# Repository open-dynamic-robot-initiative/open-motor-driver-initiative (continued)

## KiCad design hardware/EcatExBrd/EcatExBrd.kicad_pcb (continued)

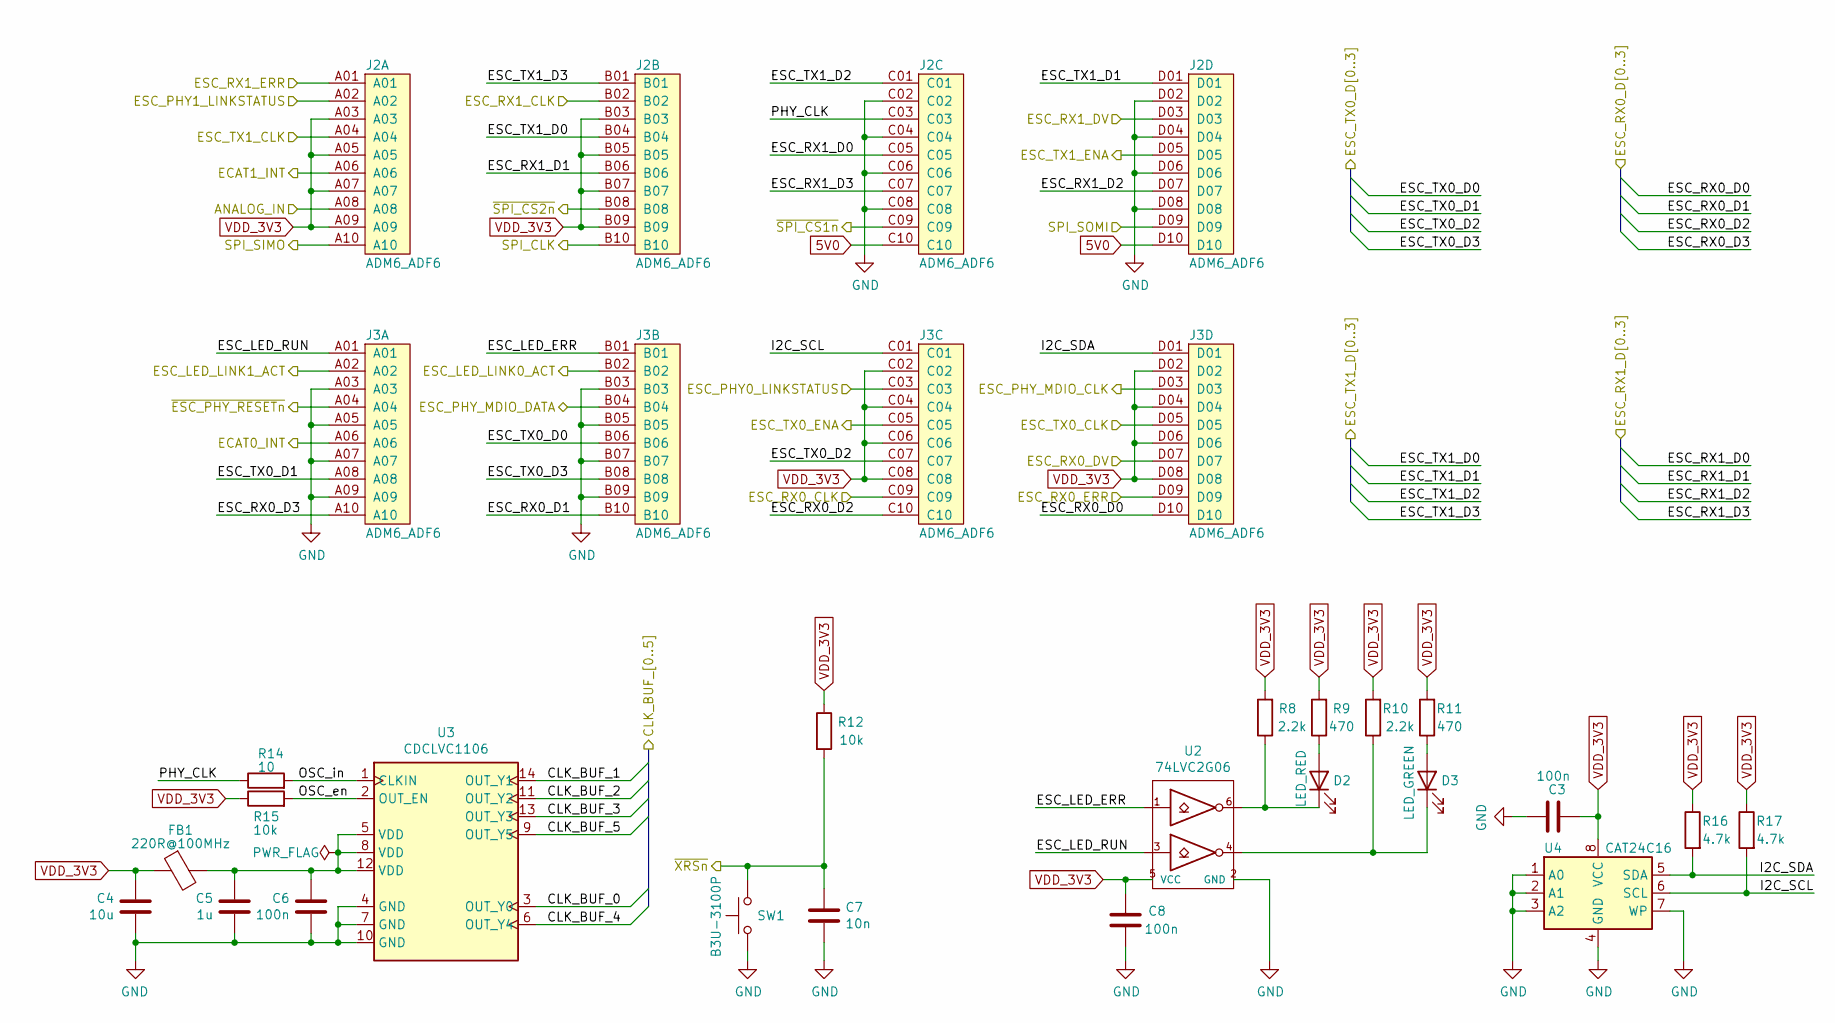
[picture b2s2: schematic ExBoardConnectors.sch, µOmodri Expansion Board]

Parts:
C3, C6, C8: 100n; C_0201_0603Metric; Part No GRM033R61C104KE84D; DigiKey 490-9985-1-ND
C4: 10u; C_0402_1005Metric; Part No GRM155R60J106ME15D; DigiKey 490-13238-1-ND
C5: 1u; C_0201_0603Metric; Part No GRM033R61A105ME15D; DigiKey 490-13226-1-ND
C7: 10n; C_0201_0603Metric; Part No GRM033R71E103KE14D; DigiKey 490-14454-1-ND
D2: LED_RED; LED_0402_1005Metric; Part No HSMC-C280; DigiKey 516-3060-1-ND
D3: LED_GREEN; LED_0402_1005Metric; Part No HSMG-C280; DigiKey 516-3066-1-ND
FB1: 220R@100MHz; L_0603_1608Metric; Part No BLM18SG221TN1D; DigiKey 490-5225-1-ND
J2, J3: ADM6_ADF6; ADM6-10-XX.X-XXX-4-X-A-XR; Part No ADM6-10-01.5-L-4-2-A-TR; DigiKey 612-ADM6-10-01.5-L-4-2-A-TR-ND
R8, R10: 2.2k; R_0201_0603Metric; Part No ERJ-1GNF2201C; DigiKey P122832CT-ND
R9, R11: 470; R_0201_0603Metric; Part No ERJ-1GNF4700C; DigiKey P123030CT-ND
R12, R15: 10k; R_0201_0603Metric; Part No ERJ-1GNF1002C; DigiKey P122414CT-ND
R14: 10; R_0201_0603Metric; Part No ERJ-1GNF10R0C; DigiKey P122669CT-ND
R16, R17: 4.7k; R_0201_0603Metric; Part No ERJ-1GNF4701C; DigiKey P123031CT-ND
SW1: B3U-3100P; SW_SPST_B3U-1000P; Part No B3U-1000P; DigiKey SW1020CT-ND
U2: 74LVC2G06; USON-6_P0.5mm_1x1.5mm; Part No SN74LVC2G06DRY; DigiKey 296-34873-1-ND
U3: CDCLVC1106; TSSOP-14_4.4x5mm_P0.65mm; Part No CDCLVC1106PWR; DigiKey 296-27588-1-ND
U4: CAT24C16; DFN-8-1EP_3x2mm_P0.5mm_EP1.3x1.5mm; Part No CAT24C16HU4I-GT3; DigiKey CAT24C16HU4I-GT3OSCT-ND

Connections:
5V0: J2.C10, J2.D10; also elsewhere on the board
/ECAT_0 - PHY/25MHz_OSC_in: U3.6 (OUT_Y4); also elsewhere on the board
/ECAT_0 - PHY/ECAT_RX_CLK: J3.C09; also elsewhere on the board
/ECAT_0 - PHY/ECAT_RX_D0: J3.D10; also elsewhere on the board
/ECAT_0 - PHY/ECAT_RX_D1: J3.B10; also elsewhere on the board
/ECAT_0 - PHY/ECAT_RX_D2: J3.C10; also elsewhere on the board
/ECAT_0 - PHY/ECAT_RX_D3: J3.A10; also elsewhere on the board
/ECAT_0 - PHY/ECAT_RX_DV: J3.D07; also elsewhere on the board
/ECAT_0 - PHY/ECAT_RX_ER: J3.D09; also elsewhere on the board
/ECAT_0 - PHY/ECAT_TX_CLK: J3.D05; also elsewhere on the board
/ECAT_0 - PHY/ECAT_TX_D0: J3.B06; also elsewhere on the board
/ECAT_0 - PHY/ECAT_TX_D1: J3.A08; also elsewhere on the board
/ECAT_0 - PHY/ECAT_TX_D2: J3.C07; also elsewhere on the board
/ECAT_0 - PHY/ECAT_TX_D3: J3.B08; also elsewhere on the board
/ECAT_0 - PHY/ECAT_TX_EN: J3.C05; also elsewhere on the board
/ECAT_1 - PHY/25MHz_OSC_in: U3.3 (OUT_Y0); also elsewhere on the board
/ECAT_1 - PHY/ECAT_RX_CLK: J2.B02; also elsewhere on the board
/ECAT_1 - PHY/ECAT_RX_D0: J2.C05; also elsewhere on the board
/ECAT_1 - PHY/ECAT_RX_D1: J2.B06; also elsewhere on the board
/ECAT_1 - PHY/ECAT_RX_D2: J2.D07; also elsewhere on the board
/ECAT_1 - PHY/ECAT_RX_D3: J2.C07; also elsewhere on the board
/ECAT_1 - PHY/ECAT_RX_DV: J2.D03; also elsewhere on the board
/ECAT_1 - PHY/ECAT_RX_ER: J2.A01; also elsewhere on the board
/ECAT_1 - PHY/ECAT_TX_CLK: J2.A04; also elsewhere on the board
/ECAT_1 - PHY/ECAT_TX_D0: J2.B04; also elsewhere on the board
/ECAT_1 - PHY/ECAT_TX_D1: J2.D01; also elsewhere on the board
/ECAT_1 - PHY/ECAT_TX_D2: J2.C01; also elsewhere on the board
/ECAT_1 - PHY/ECAT_TX_D3: J2.B01; also elsewhere on the board
/ECAT_1 - PHY/ECAT_TX_EN: J2.D05; also elsewhere on the board
/ECAT_Extension/ANALOG_IN: J2.A08; also elsewhere on the board
/ECAT_Extension/ECAT0_INT: J3.A06; also elsewhere on the board
/ECAT_Extension/ECAT1_INT: J2.A06; also elsewhere on the board
/ECAT_Extension/ESC_LED_ERR: J3.B01, U2.1
/ECAT_Extension/ESC_LED_LINK0_ACT: J3.B02; also elsewhere on the board
/ECAT_Extension/ESC_LED_LINK1_ACT: J3.A02; also elsewhere on the board
/ECAT_Extension/ESC_LED_RUN: J3.A01, U2.3
/ECAT_Extension/ESC_PHY0_LINKSTATUS: J3.C03; also elsewhere on the board
/ECAT_Extension/ESC_PHY1_LINKSTATUS: J2.A02; also elsewhere on the board
/ECAT_Extension/ESC_PHY_MDIO_CLK: J3.D03; also elsewhere on the board
/ECAT_Extension/ESC_PHY_MDIO_DATA: J3.B04; also elsewhere on the board
/ECAT_Extension/I2C_SCL: J3.C01, R17.2, U4.6 (SCL)
/ECAT_Extension/I2C_SDA: J3.D01, R16.2, U4.5 (SDA)
/ECAT_Extension/OSC_en: R15.2, U3.2 (OUT_EN)
/ECAT_Extension/OSC_in: R14.2, U3.1 (CLKIN)
/ECAT_Extension/PHY_CLK: J2.C03, R14.1
/ECAT_Extension/~ESC_PHY_RESETn~: J3.A04; also elsewhere on the board
/ECAT_Extension/~SPI_CS1n~: J2.C09; also elsewhere on the board
/ECAT_Extension/~SPI_CS2n~: J2.B08; also elsewhere on the board
/Sensor Channel #1/25MHz_OSC_in_1: U3.13 (OUT_Y3); also elsewhere on the board
/Sensor Channel #1/25MHz_OSC_in_2: U3.14 (OUT_Y1); also elsewhere on the board
/Sensor Channel #1/MISO: J2.D09; also elsewhere on the board
/Sensor Channel #1/MOSI: J2.A10; also elsewhere on the board
/Sensor Channel #1/SCLK: J2.B10; also elsewhere on the board
/Sensor Channel #1/~RST_n~: C7.1, R12.2, SW1.2; also elsewhere on the board
/Sensor Channel #2/25MHz_OSC_in_1: U3.9 (OUT_Y5); also elsewhere on the board
/Sensor Channel #2/25MHz_OSC_in_2: U3.11 (OUT_Y2); also elsewhere on the board
GND: C3.1, C4.2, C5.2, C6.2, C7.2, C8.2, J2.C02, J2.C04, J2.C06, J2.C08, J2.D02, J2.D04, J2.D06, J2.D08, J3.A03, J3.A05, J3.A07, J3.A09, J3.B03, J3.B05, J3.B07, J3.B09, SW1.1, U2.2 (GND), U3.4 (GND), U3.7 (GND), U3.10 (GND), U4.1 (A0), U4.2 (A1), U4.3 (A2), U4.4 (GND), U4.7 (WP), U4.9 (GND); also elsewhere on the board
unnamed: C5.1, C6.1, FB1.2, U3.5 (VDD), U3.8 (VDD), U3.12 (VDD)
unnamed: D2.1 (K), R8.1, U2.6
unnamed: D2.2 (A), R9.1
unnamed: D3.1 (K), R10.1, U2.4
unnamed: D3.2 (A), R11.1
VDD_3V3: C3.2, C4.1, C8.1, FB1.1, J2.A03, J2.A05, J2.A07, J2.A09, J2.B03, J2.B05, J2.B07, J2.B09, J3.C02, J3.C04, J3.C06, J3.C08, J3.D02, J3.D04, J3.D06, J3.D08, R8.2, R9.2, R10.2, R11.2, R12.1, R15.1, R16.1, R17.1, U2.5 (VCC), U4.8 (VCC); also elsewhere on the board

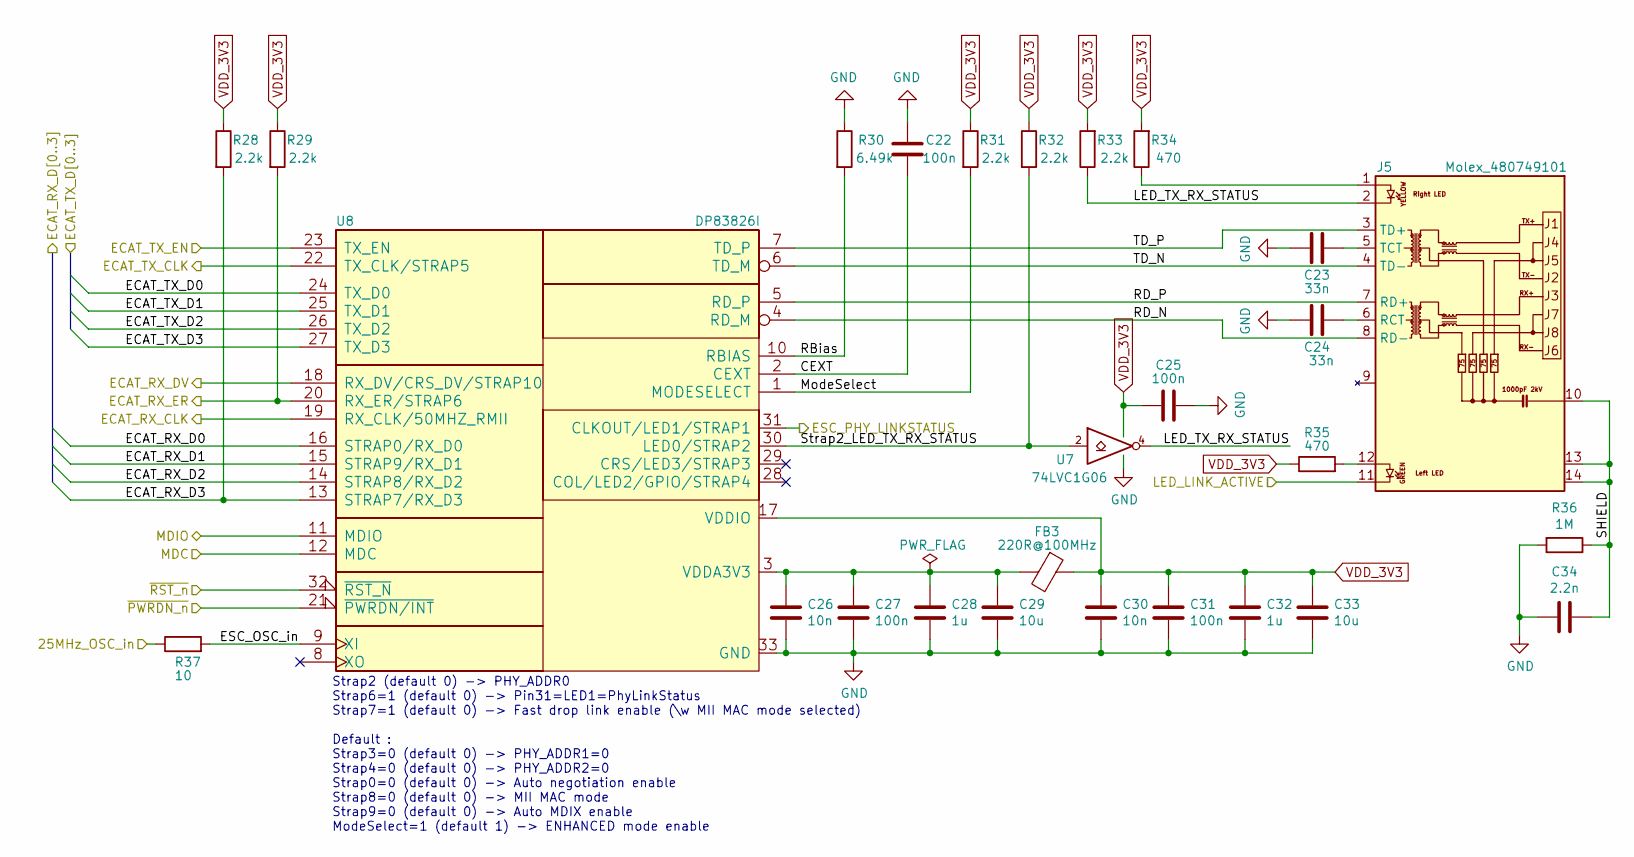
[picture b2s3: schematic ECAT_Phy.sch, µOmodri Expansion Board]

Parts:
C9, C12, C14, C18: 100n; C_0201_0603Metric; Part No GRM033R61C104KE84D; DigiKey 490-9985-1-ND
C10, C11: 33n; C_0201_0603Metric; Part No GRM033R61C333KE84D; DigiKey 490-7226-1-ND
C13, C17: 10n; C_0201_0603Metric; Part No GRM033R71E103KE14D; DigiKey 490-14454-1-ND
C15, C19: 1u; C_0201_0603Metric; Part No GRM033R61A105ME15D; DigiKey 490-13226-1-ND
C16, C20: 10u; C_0402_1005Metric; Part No GRM155R60J106ME15D; DigiKey 490-13238-1-ND
C21: 2.2n; C_0603_1608Metric; Part No GRM188R72D222KW07D; DigiKey 490-16804-1-ND
FB2: 220R@100MHz; L_0603_1608Metric; Part No BLM18SG221TN1D; DigiKey 490-5225-1-ND
J4: Molex_480749101; RJ45_Molex_48074-9101_Horizontal; Part No 48074-9101; DigiKey WM17279CT-ND
R18, R19, R21, R22, R23: 2.2k; R_0201_0603Metric; Part No ERJ-1GNF2201C; DigiKey P122832CT-ND
R20: 6.49k; R_0201_0603Metric; Part No ERJ-1GNF6491C; DigiKey P123115CT-ND
R24, R25: 470; R_0201_0603Metric; Part No ERJ-1GNF4700C; DigiKey P123030CT-ND
R26: 1M; R_0805_2012Metric; Part No ERJ-6ENF1004V; DigiKey P1.00MCCT-ND
R27: 10; R_0201_0603Metric; Part No ERJ-1GNF10R0C; DigiKey P122669CT-ND
U5: 74LVC1G06; USON-6_P0.5mm_1x1.5mm; Part No SN74LVC1G06DRY; DigiKey 296-29047-1-ND
U6: DP83826I; VQFN-32-1EP_5x5mm_P0.5mm_EP2.2x2.2mm; Part No DP83826IRHBR; DigiKey 296-DP83826IRHBRCT-ND

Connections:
/ECAT_0 - PHY/25MHz_OSC_in: R27.1; also elsewhere on the board
/ECAT_0 - PHY/CEXT: C9.1, U6.2 (CEXT)
/ECAT_0 - PHY/ECAT_RX_CLK: U6.19 (RX_CLK/50MHZ_RMII); also elsewhere on the board
/ECAT_0 - PHY/ECAT_RX_D0: U6.16 (STRAP0/RX_D0); also elsewhere on the board
/ECAT_0 - PHY/ECAT_RX_D1: U6.15 (STRAP9/RX_D1); also elsewhere on the board
/ECAT_0 - PHY/ECAT_RX_D2: U6.14 (STRAP8/RX_D2); also elsewhere on the board
/ECAT_0 - PHY/ECAT_RX_D3: R18.2, U6.13 (STRAP7/RX_D3); also elsewhere on the board
/ECAT_0 - PHY/ECAT_RX_DV: U6.18 (RX_DV/CRS_DV/STRAP10); also elsewhere on the board
/ECAT_0 - PHY/ECAT_RX_ER: R19.2, U6.20 (RX_ER/STRAP6); also elsewhere on the board
/ECAT_0 - PHY/ECAT_TX_CLK: U6.22 (TX_CLK/STRAP5); also elsewhere on the board
/ECAT_0 - PHY/ECAT_TX_D0: U6.24 (TX_D0); also elsewhere on the board
/ECAT_0 - PHY/ECAT_TX_D1: U6.25 (TX_D1); also elsewhere on the board
/ECAT_0 - PHY/ECAT_TX_D2: U6.26 (TX_D2); also elsewhere on the board
/ECAT_0 - PHY/ECAT_TX_D3: U6.27 (TX_D3); also elsewhere on the board
/ECAT_0 - PHY/ECAT_TX_EN: U6.23 (TX_EN); also elsewhere on the board
/ECAT_0 - PHY/ESC_OSC_in: R27.2, U6.9 (XI)
/ECAT_0 - PHY/LED_TX_RX_STATUS: J4.2, R23.1, U5.4
/ECAT_0 - PHY/ModeSelect: R21.2, U6.1 (MODESELECT)
/ECAT_0 - PHY/RBias: R20.2, U6.10 (RBIAS)
/ECAT_0 - PHY/RD_N: J4.8 (RD-), U6.4 (RD_M)
/ECAT_0 - PHY/RD_P: J4.7 (RD+), U6.5 (RD_P)
/ECAT_0 - PHY/SHIELD: C21.1, J4.10, J4.13, J4.14, R26.1
/ECAT_0 - PHY/Strap2_LED_TX_RX_STATUS: R22.2, U5.2, U6.30 (LED0/STRAP2)
/ECAT_0 - PHY/TD_N: J4.4 (TD-), U6.6 (TD_M)
/ECAT_0 - PHY/TD_P: J4.3 (TD+), U6.7 (TD_P)
/ECAT_Extension/ECAT0_INT: U6.21 (~PWRDN/INT~); also elsewhere on the board
/ECAT_Extension/ESC_LED_LINK0_ACT: J4.11; also elsewhere on the board
/ECAT_Extension/ESC_PHY0_LINKSTATUS: U6.31 (CLKOUT/LED1/STRAP1); also elsewhere on the board
/ECAT_Extension/ESC_PHY_MDIO_CLK: U6.12 (MDC); also elsewhere on the board
/ECAT_Extension/ESC_PHY_MDIO_DATA: U6.11 (MDIO); also elsewhere on the board
/ECAT_Extension/~ESC_PHY_RESETn~: U6.32 (~RST_N~); also elsewhere on the board
GND: C9.2, C10.2, C11.2, C12.1, C13.2, C14.2, C15.2, C16.2, C17.2, C18.2, C19.2, C20.2, C21.2, R20.1, R26.2, U5.3 (GND), U6.33 (GND); also elsewhere on the board
unnamed: C10.1, J4.5 (TCT)
unnamed: C11.1, J4.6 (RCT)
unnamed: C13.1, C14.1, C15.1, C16.1, FB2.2, U6.3 (VDDA3V3)
unnamed: J4.1, R24.1
unnamed: J4.12, R25.2
VDD_3V3: C12.2, C17.1, C18.1, C19.1, C20.1, FB2.1, R18.1, R19.1, R21.1, R22.1, R23.2, R24.2, R25.1, U5.6 (VCC), U6.17 (VDDIO); also elsewhere on the board

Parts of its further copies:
C22, C25, C27, C31: 100n; C_0201_0603Metric; Part No GRM033R61C104KE84D; DigiKey 490-9985-1-ND
C23, C24: 33n; C_0201_0603Metric; Part No GRM033R61C333KE84D; DigiKey 490-7226-1-ND
C26, C30: 10n; C_0201_0603Metric; Part No GRM033R71E103KE14D; DigiKey 490-14454-1-ND
C28, C32: 1u; C_0201_0603Metric; Part No GRM033R61A105ME15D; DigiKey 490-13226-1-ND
C29, C33: 10u; C_0402_1005Metric; Part No GRM155R60J106ME15D; DigiKey 490-13238-1-ND
C34: 2.2n; C_0603_1608Metric; Part No GRM188R72D222KW07D; DigiKey 490-16804-1-ND
FB3: 220R@100MHz; L_0603_1608Metric; Part No BLM18SG221TN1D; DigiKey 490-5225-1-ND
J5: Molex_480749101; RJ45_Molex_48074-9101_Horizontal; Part No 48074-9101; DigiKey WM17279CT-ND
R28, R29, R31, R32, R33: 2.2k; R_0201_0603Metric; Part No ERJ-1GNF2201C; DigiKey P122832CT-ND
R30: 6.49k; R_0201_0603Metric; Part No ERJ-1GNF6491C; DigiKey P123115CT-ND
R34, R35: 470; R_0201_0603Metric; Part No ERJ-1GNF4700C; DigiKey P123030CT-ND
R36: 1M; R_0805_2012Metric; Part No ERJ-6ENF1004V; DigiKey P1.00MCCT-ND
R37: 10; R_0201_0603Metric; Part No ERJ-1GNF10R0C; DigiKey P122669CT-ND
U7: 74LVC1G06; USON-6_P0.5mm_1x1.5mm; Part No SN74LVC1G06DRY; DigiKey 296-29047-1-ND
U8: DP83826I; VQFN-32-1EP_5x5mm_P0.5mm_EP2.2x2.2mm; Part No DP83826IRHBR; DigiKey 296-DP83826IRHBRCT-ND

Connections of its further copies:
/ECAT_1 - PHY/25MHz_OSC_in: R37.1; also elsewhere on the board
/ECAT_1 - PHY/CEXT: C22.1, U8.2 (CEXT)
/ECAT_1 - PHY/ECAT_RX_CLK: U8.19 (RX_CLK/50MHZ_RMII); also elsewhere on the board
/ECAT_1 - PHY/ECAT_RX_D0: U8.16 (STRAP0/RX_D0); also elsewhere on the board
/ECAT_1 - PHY/ECAT_RX_D1: U8.15 (STRAP9/RX_D1); also elsewhere on the board
/ECAT_1 - PHY/ECAT_RX_D2: U8.14 (STRAP8/RX_D2); also elsewhere on the board
/ECAT_1 - PHY/ECAT_RX_D3: R28.2, U8.13 (STRAP7/RX_D3); also elsewhere on the board
/ECAT_1 - PHY/ECAT_RX_DV: U8.18 (RX_DV/CRS_DV/STRAP10); also elsewhere on the board
/ECAT_1 - PHY/ECAT_RX_ER: R29.2, U8.20 (RX_ER/STRAP6); also elsewhere on the board
/ECAT_1 - PHY/ECAT_TX_CLK: U8.22 (TX_CLK/STRAP5); also elsewhere on the board
/ECAT_1 - PHY/ECAT_TX_D0: U8.24 (TX_D0); also elsewhere on the board
/ECAT_1 - PHY/ECAT_TX_D1: U8.25 (TX_D1); also elsewhere on the board
/ECAT_1 - PHY/ECAT_TX_D2: U8.26 (TX_D2); also elsewhere on the board
/ECAT_1 - PHY/ECAT_TX_D3: U8.27 (TX_D3); also elsewhere on the board
/ECAT_1 - PHY/ECAT_TX_EN: U8.23 (TX_EN); also elsewhere on the board
/ECAT_1 - PHY/ESC_OSC_in: R37.2, U8.9 (XI)
/ECAT_1 - PHY/LED_TX_RX_STATUS: J5.2, R33.1, U7.4
/ECAT_1 - PHY/ModeSelect: R31.2, U8.1 (MODESELECT)
/ECAT_1 - PHY/RBias: R30.2, U8.10 (RBIAS)
/ECAT_1 - PHY/RD_N: J5.8 (RD-), U8.4 (RD_M)
/ECAT_1 - PHY/RD_P: J5.7 (RD+), U8.5 (RD_P)
/ECAT_1 - PHY/SHIELD: C34.1, J5.10, J5.13, J5.14, R36.1
/ECAT_1 - PHY/Strap2_LED_TX_RX_STATUS: R32.2, U7.2, U8.30 (LED0/STRAP2)
/ECAT_1 - PHY/TD_N: J5.4 (TD-), U8.6 (TD_M)
/ECAT_1 - PHY/TD_P: J5.3 (TD+), U8.7 (TD_P)
/ECAT_Extension/ECAT1_INT: U8.21 (~PWRDN/INT~); also elsewhere on the board
/ECAT_Extension/ESC_LED_LINK1_ACT: J5.11; also elsewhere on the board
/ECAT_Extension/ESC_PHY1_LINKSTATUS: U8.31 (CLKOUT/LED1/STRAP1); also elsewhere on the board
/ECAT_Extension/ESC_PHY_MDIO_CLK: U8.12 (MDC); also elsewhere on the board
/ECAT_Extension/ESC_PHY_MDIO_DATA: U8.11 (MDIO); also elsewhere on the board
/ECAT_Extension/~ESC_PHY_RESETn~: U8.32 (~RST_N~); also elsewhere on the board
GND: C22.2, C23.2, C24.2, C25.1, C26.2, C27.2, C28.2, C29.2, C30.2, C31.2, C32.2, C33.2, C34.2, R30.1, R36.2, U7.3 (GND), U8.33 (GND); also elsewhere on the board
unnamed: C23.1, J5.5 (TCT)
unnamed: C24.1, J5.6 (RCT)
unnamed: C26.1, C27.1, C28.1, C29.1, FB3.2, U8.3 (VDDA3V3)
unnamed: J5.1, R34.1
unnamed: J5.12, R35.2
VDD_3V3: C25.2, C30.1, C31.1, C32.1, C33.1, FB3.1, R28.1, R29.1, R31.1, R32.1, R33.2, R34.2, R35.1, U7.6 (VCC), U8.17 (VDDIO); also elsewhere on the board

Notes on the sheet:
Strap2 (default 0) -> PHY_ADDR0 Strap6=1 (default 0) -> Pin31=LED1=PhyLinkStatus Strap7=1 (default 0) -> Fast drop link enable (\w MII MAC mode selected) Default : Strap3=0 (default 0) -> PHY_ADDR1=0 Strap4=0 (default 0) -> PHY_ADDR2=0 Strap0=0 (default 0) -> Auto negotiation enable Strap8=0 (defau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

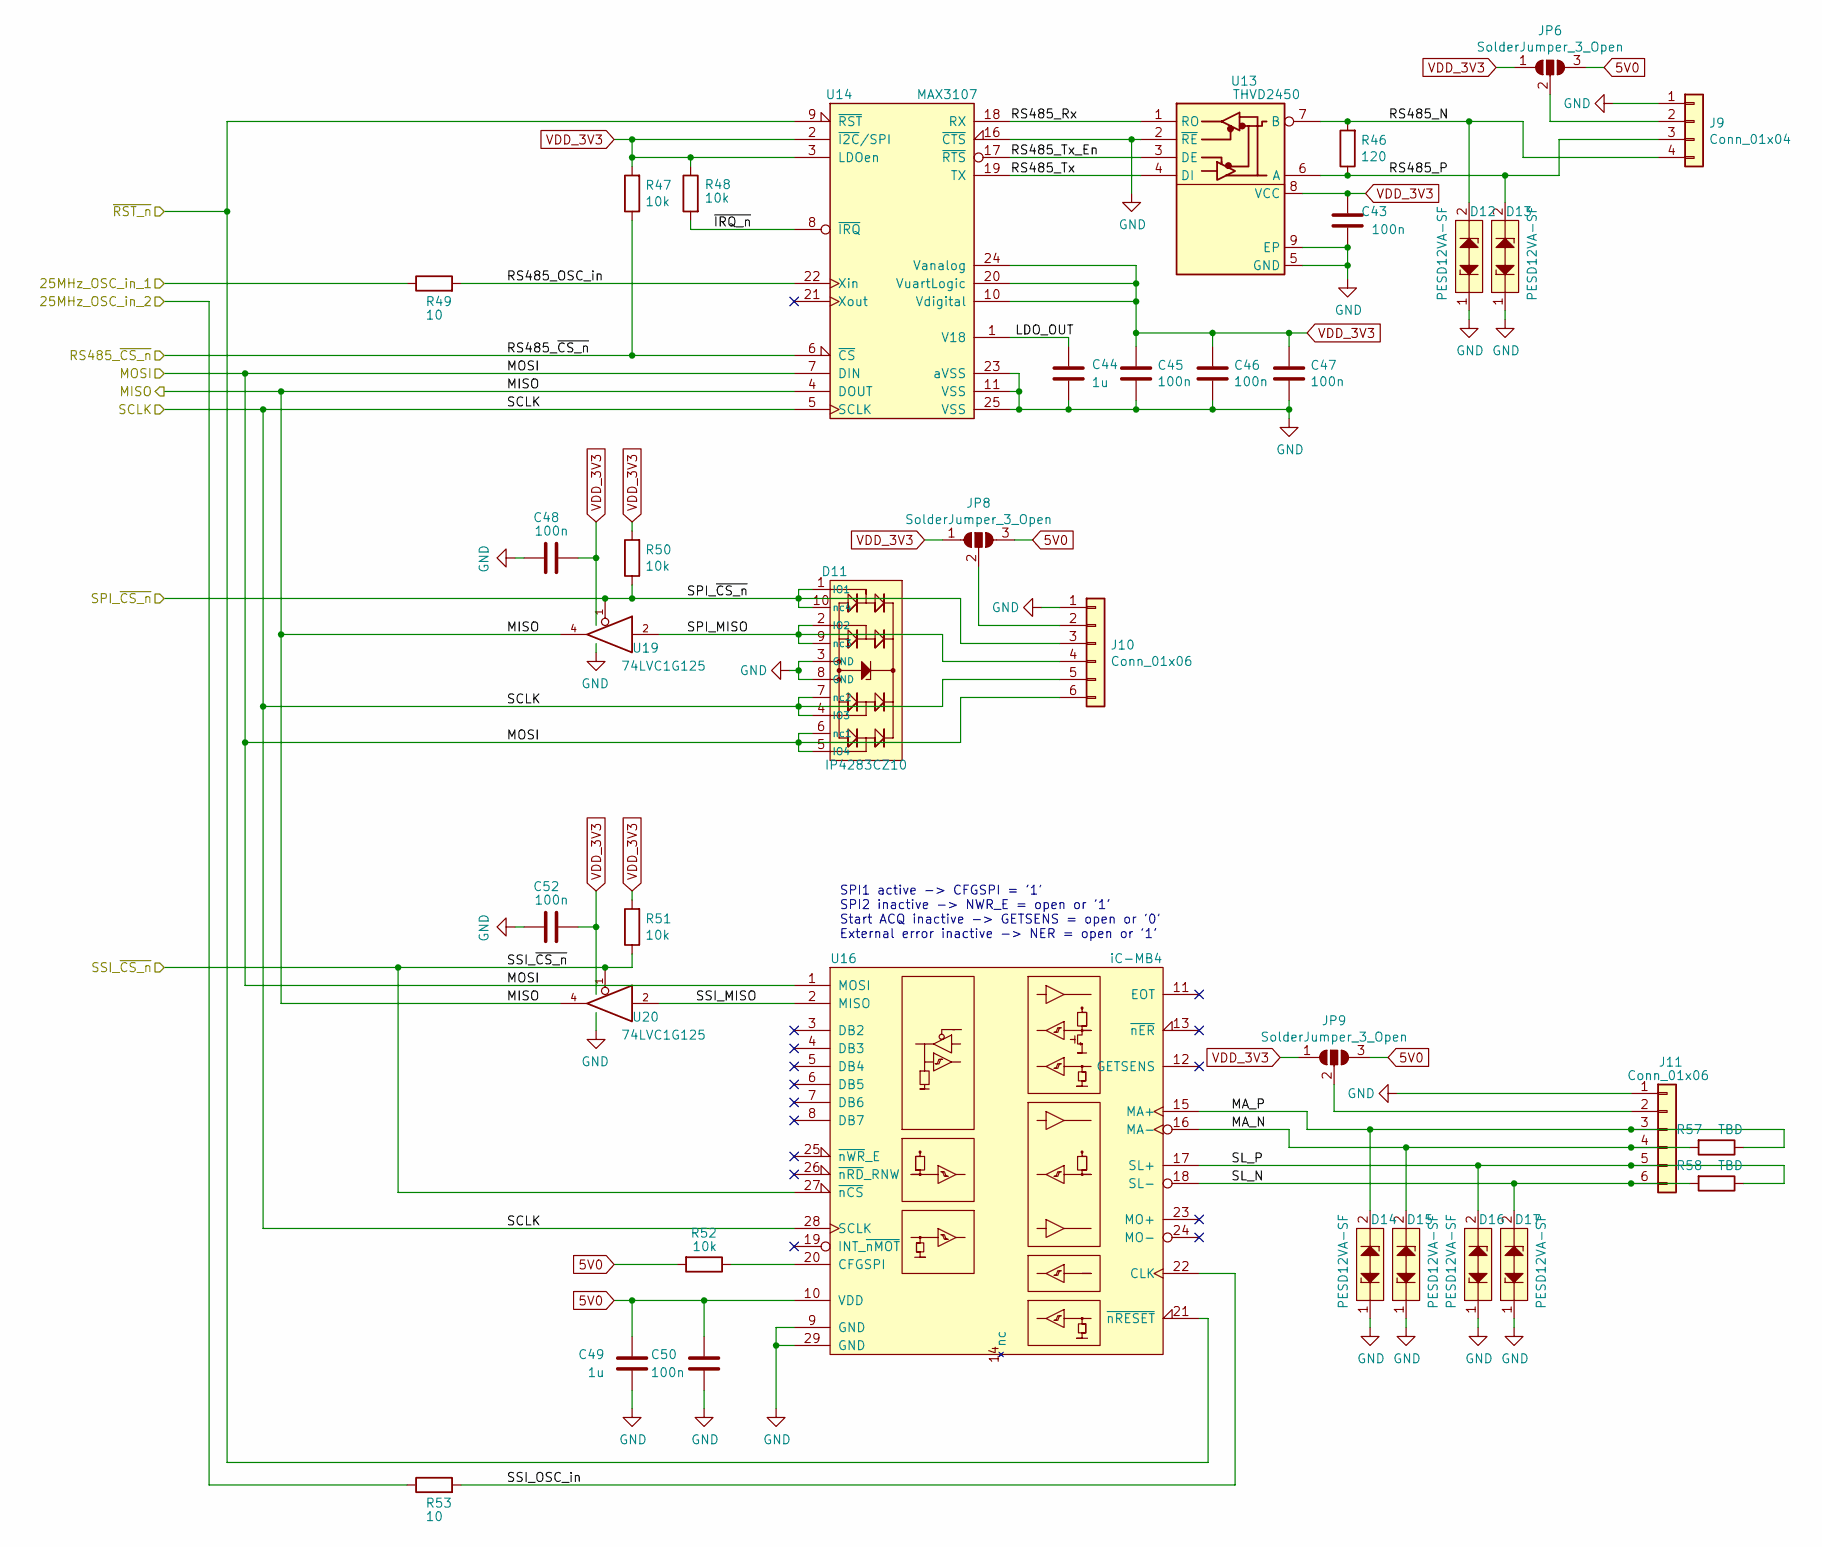
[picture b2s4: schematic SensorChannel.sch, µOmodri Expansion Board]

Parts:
C43, C45, C46, C47, C48, C50, C52: 100n; C_0201_0603Metric; Part No GRM033R61C104KE84D; DigiKey 490-9985-1-ND
C44, C49: 1u; C_0201_0603Metric; Part No GRM033R61A105ME15D; DigiKey 490-13226-1-ND
D11: IP4283CZ10; Diodes_DFN2510A-10_1.0x2.5mm_P0.5mm; Part No IP4283CZ10-TBR; DigiKey 1727-1272-1-ND
D12, D13, D14, D15, D16, D17: PESD12VA-SF; Diodes_DSN0603-2_0.6x0.3mm_P0.4mm; Part No PESD12VA-SFYL; DigiKey 1727-8648-1-ND
J9: Conn_01x04; Hirose_DF13-04P-1.25DSA_1x04_P1.25mm_Vertical; Part No DF13-4P-1.25DSA; DigiKey H2193-ND
J10, J11: Conn_01x06; Hirose_DF13-06P-1.25DSA_1x06_P1.25mm_Vertical; Part No DF13-6P-1.25DSA; DigiKey H2195-ND
JP6, JP8, JP9: SolderJumper_3_Open; SolderJumper-3_0201_0603Metric_Open_Pad; Part No ERJ-1GN0R00C; DigiKey P15979CT-ND
R46: 120; R_0201_0603Metric; Part No ERJ-1GNF1200C; DigiKey P122692CT-ND
R47, R48, R50, R51, R52: 10k; R_0201_0603Metric; Part No ERJ-1GNF1002C; DigiKey P122414CT-ND
R49, R53: 10; R_0201_0603Metric; Part No ERJ-1GNF10R0C; DigiKey P122669CT-ND
R57, R58: TBD; R_0201_0603Metric
U13: THVD2450; TDFN-8-1EP_3.0x3.0mm_P0.65mm; Part No THVD2450DRBR; DigiKey 296-THVD2450DRBRCT-ND
U14: MAX3107; TQFN-24-1EP_3.5x3.5mm_P0.4mm_EP2.4x2.4mm; Part No MAX3107ETG+; DigiKey MAX3107ETG+-ND
U16: iC-MB4; TQFN-28-1EP_5x5mm_P0.5mm_EP3.1x3.1mm; Part No iC-MB4
U19, U20: 74LVC1G125; USON-6_P0.5mm_1x1.5mm

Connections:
5V0: C49.2, C50.1, JP6.3 (B), JP8.3 (B), JP9.3 (B), R52.2, U16.10 (VDD); also elsewhere on the board
/Sensor Channel #1/25MHz_OSC_in_1: R49.1; also elsewhere on the board
/Sensor Channel #1/25MHz_OSC_in_2: R53.1; also elsewhere on the board
/Sensor Channel #1/LDO_OUT: C44.1, U14.1 (V18)
/Sensor Channel #1/MA_N: D15.2, J11.4, R57.2, U16.16 (MA-)
/Sensor Channel #1/MA_P: D14.2, J11.3, R57.1, U16.15 (MA+)
/Sensor Channel #1/MISO: U14.4 (DOUT), U19.4, U20.4; also elsewhere on the board
/Sensor Channel #1/MOSI: D11.5 (IO4), D11.6 (nc1), J10.6, U14.7 (DIN), U16.1 (MOSI); also elsewhere on the board
/Sensor Channel #1/RS485_N: D12.2, J9.4, R46.2, U13.7 (B)
/Sensor Channel #1/RS485_OSC_in: R49.2, U14.22 (Xin)
/Sensor Channel #1/RS485_P: D13.2, J9.3, R46.1, U13.6 (A)
/Sensor Channel #1/RS485_Rx: U13.1 (RO), U14.18 (RX)
/Sensor Channel #1/RS485_Tx: U13.4 (DI), U14.19 (TX)
/Sensor Channel #1/RS485_Tx_En: U13.3 (DE), U14.17 (~RTS)
/Sensor Channel #1/RS485_~CS_n~: R47.1, U14.6 (~CS~); also elsewhere on the board
/Sensor Channel #1/SCLK: D11.4 (IO3), D11.7 (nc2), J10.5, U14.5 (SCLK), U16.28 (SCLK); also elsewhere on the board
/Sensor Channel #1/SL_N: D17.2, J11.6, R58.2, U16.18 (SL-)
/Sensor Channel #1/SL_P: D16.2, J11.5, R58.1, U16.17 (SL+)
/Sensor Channel #1/SPI_MISO: D11.2 (IO2), D11.9 (nc3), J10.4, U19.2
/Sensor Channel #1/SPI_~CS_n~: D11.1 (IO1), D11.10 (nc4), J10.3, R50.1, U19.1; also elsewhere on the board
/Sensor Channel #1/SSI_MISO: U16.2 (MISO), U20.2
/Sensor Channel #1/SSI_OSC_in: R53.2, U16.22 (CLK)
/Sensor Channel #1/SSI_~CS_n~: R51.1, U16.27 (~nCS~), U20.1; also elsewhere on the board
/Sensor Channel #1/~IRQ_n~: R48.2, U14.8 (~IRQ~)
/Sensor Channel #1/~RST_n~: U14.9 (~RST~), U16.21 (~nRESET~); also elsewhere on the board
GND: C43.1, C44.2, C45.2, C46.2, C47.2, C48.1, C49.1, C50.2, C52.1, D11.3 (GND), D11.8 (GND), D12.1, D13.1, D14.1, D15.1, D16.1, D17.1, J9.1, J10.1, J11.1, U13.2 (~RE~), U13.5 (GND), U13.9 (EP), U14.11 (VSS), U14.16 (~CTS~), U14.23 (aVSS), U14.25 (VSS), U16.9 (GND), U16.29 (GND), U19.3 (GND), U20.3 (GND); also elsewhere on the board
unnamed: J9.2, JP6.2 (C)
unnamed: J10.2, JP8.2 (C)
unnamed: J11.2, JP9.2 (C)
unnamed: R52.1, U16.20 (CFGSPI)
VDD_3V3: C43.2, C45.1, C46.1, C47.1, C48.2, C52.2, JP6.1 (A), JP8.1 (A), JP9.1 (A), R47.2, R48.1, R50.2, R51.2, U13.8 (VCC), U14.2 (~I2C~/SPI), U14.3 (LDOen), U14.10 (Vdigital), U14.20 (VuartLogic), U14.24 (Vanalog), U19.6 (VCC), U20.6 (VCC); also elsewhere on the board

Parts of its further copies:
C35, C37, C38, C39, C40, C42, C51: 100n; C_0201_0603Metric; Part No GRM033R61C104KE84D; DigiKey 490-9985-1-ND
C36, C41: 1u; C_0201_0603Metric; Part No GRM033R61A105ME15D; DigiKey 490-13226-1-ND
D4, D5, D7, D8, D9, D10: PESD12VA-SF; Diodes_DSN0603-2_0.6x0.3mm_P0.4mm; Part No PESD12VA-SFYL; DigiKey 1727-8648-1-ND
D6: IP4283CZ10; Diodes_DFN2510A-10_1.0x2.5mm_P0.5mm; Part No IP4283CZ10-TBR; DigiKey 1727-1272-1-ND
J6: Conn_01x04; Hirose_DF13-04P-1.25DSA_1x04_P1.25mm_Vertical; Part No DF13-4P-1.25DSA; DigiKey H2193-ND
J7, J8: Conn_01x06; Hirose_DF13-06P-1.25DSA_1x06_P1.25mm_Vertical; Part No DF13-6P-1.25DSA; DigiKey H2195-ND
JP2, JP4, JP5: SolderJumper_3_Open; SolderJumper-3_0201_0603Metric_Open_Pad; Part No ERJ-1GN0R00C; DigiKey P15979CT-ND
R38: 120; R_0201_0603Metric; Part No ERJ-1GNF1200C; DigiKey P122692CT-ND
R39, R40, R42, R43, R44: 10k; R_0201_0603Metric; Part No ERJ-1GNF1002C; DigiKey P122414CT-ND
R41, R45: 10; R_0201_0603Metric; Part No ERJ-1GNF10R0C; DigiKey P122669CT-ND
R54, R55: TBD; R_0201_0603Metric
U9: THVD2450; TDFN-8-1EP_3.0x3.0mm_P0.65mm; Part No THVD2450DRBR; DigiKey 296-THVD2450DRBRCT-ND
U10: MAX3107; TQFN-24-1EP_3.5x3.5mm_P0.4mm_EP2.4x2.4mm; Part No MAX3107ETG+; DigiKey MAX3107ETG+-ND
U12: iC-MB4; TQFN-28-1EP_5x5mm_P0.5mm_EP3.1x3.1mm; Part No iC-MB4
U17, U18: 74LVC1G125; USON-6_P0.5mm_1x1.5mm

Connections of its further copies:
5V0: C41.2, C42.1, JP2.3 (B), JP4.3 (B), JP5.3 (B), R44.2, U12.10 (VDD); also elsewhere on the board
/Sensor Channel #1/MISO: U10.4 (DOUT), U17.4, U18.4; also elsewhere on the board
/Sensor Channel #1/MOSI: D6.5 (IO4), D6.6 (nc1), J7.6, U10.7 (DIN), U12.1 (MOSI); also elsewhere on the board
/Sensor Channel #1/SCLK: D6.4 (IO3), D6.7 (nc2), J7.5, U10.5 (SCLK), U12.28 (SCLK); also elsewhere on the board
/Sensor Channel #1/~RST_n~: U10.9 (~RST~), U12.21 (~nRESET~); also elsewhere on the board
/Sensor Channel #2/25MHz_OSC_in_1: R41.1; also elsewhere on the board
/Sensor Channel #2/25MHz_OSC_in_2: R45.1; also elsewhere on the board
/Sensor Channel #2/LDO_OUT: C36.1, U10.1 (V18)
/Sensor Channel #2/MA_N: D8.2, J8.4, R54.2, U12.16 (MA-)
/Sensor Channel #2/MA_P: D7.2, J8.3, R54.1, U12.15 (MA+)
/Sensor Channel #2/RS485_N: D4.2, J6.4, R38.2, U9.7 (B)
/Sensor Channel #2/RS485_OSC_in: R41.2, U10.22 (Xin)
/Sensor Channel #2/RS485_P: D5.2, J6.3, R38.1, U9.6 (A)
/Sensor Channel #2/RS485_Rx: U9.1 (RO), U10.18 (RX)
/Sensor Channel #2/RS485_Tx: U9.4 (DI), U10.19 (TX)
/Sensor Channel #2/RS485_Tx_En: U9.3 (DE), U10.17 (~RTS)
/Sensor Channel #2/RS485_~CS_n~: R39.1, U10.6 (~CS~); also elsewhere on the board
/Sensor Channel #2/SL_N: D10.2, J8.6, R55.2, U12.18 (SL-)
/Sensor Channel #2/SL_P: D9.2, J8.5, R55.1, U12.17 (SL+)
/Sensor Channel #2/SPI_MISO: D6.2 (IO2), D6.9 (nc3), J7.4, U17.2
/Sensor Channel #2/SPI_~CS_n~: D6.1 (IO1), D6.10 (nc4), J7.3, R42.1, U17.1; also elsewhere on the board
/Sensor Channel #2/SSI_MISO: U12.2 (MISO), U18.2
/Sensor Channel #2/SSI_OSC_in: R45.2, U12.22 (CLK)
/Sensor Channel #2/SSI_~CS_n~: R43.1, U12.27 (~nCS~), U18.1; also elsewhere on the board
/Sensor Channel #2/~IRQ_n~: R40.2, U10.8 (~IRQ~)
GND: C35.1, C36.2, C37.2, C38.2, C39.2, C40.1, C41.1, C42.2, C51.1, D4.1, D5.1, D6.3 (GND), D6.8 (GND), D7.1, D8.1, D9.1, D10.1, J6.1, J7.1, J8.1, U9.2 (~RE~), U9.5 (GND), U9.9 (EP), U10.11 (VSS), U10.16 (~CTS~), U10.23 (aVSS), U10.25 (VSS), U12.9 (GND), U12.29 (GND), U17.3 (GND), U18.3 (GND); also elsewhere on the board
unnamed: J6.2, JP2.2 (C)
unnamed: J7.2, JP4.2 (C)
unnamed: J8.2, JP5.2 (C)
unnamed: R44.1, U12.20 (CFGSPI)
VDD_3V3: C35.2, C37.1, C38.1, C39.1, C40.2, C51.2, JP2.1 (A), JP4.1 (A), JP5.1 (A), R39.2, R40.1, R42.2, R43.2, U9.8 (VCC), U10.2 (~I2C~/SPI), U10.3 (LDOen), U10.10 (Vdigital), U10.20 (VuartLogic), U10.24 (Vanalog), U17.6 (VCC), U18.6 (VCC); also elsewhere on the board

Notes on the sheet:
SPI1 active -> CFGSPI = '1' SPI2 inactive -> NWR_E = open or '1' Start ACQ inactive -> GETSENS = open or '0' External error inactive -> NER = open or '1'

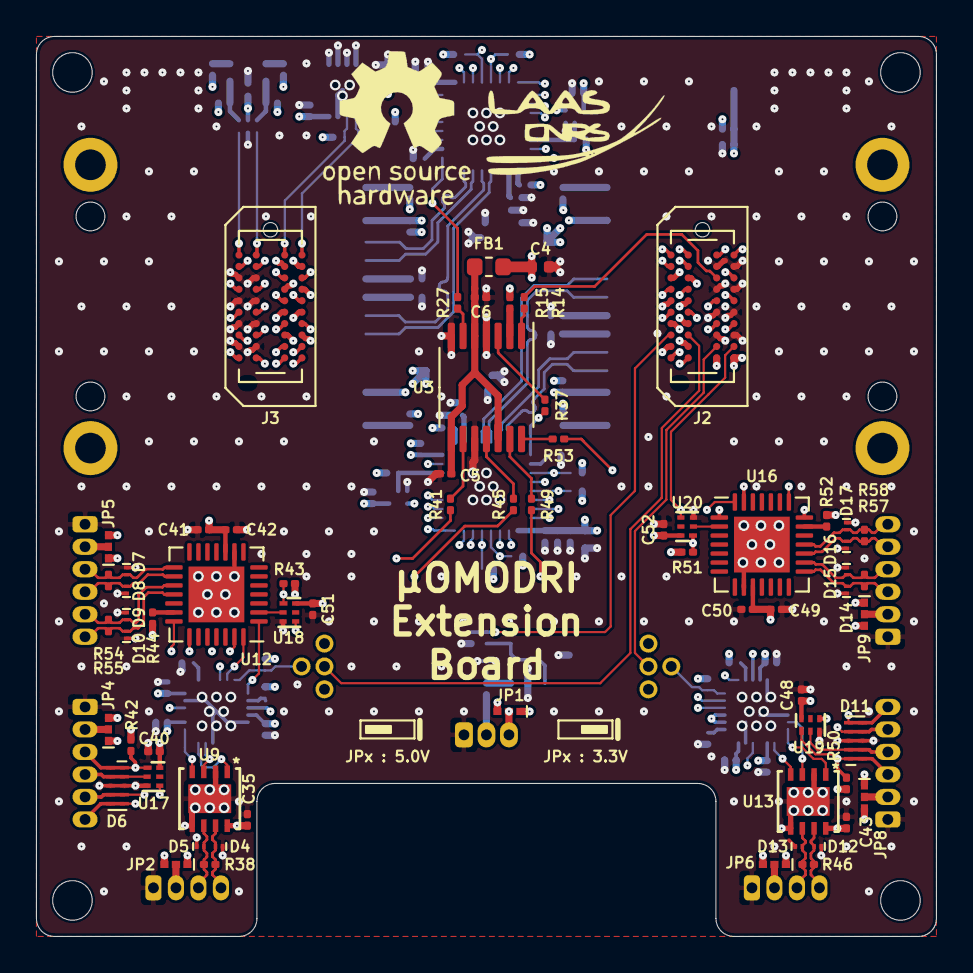
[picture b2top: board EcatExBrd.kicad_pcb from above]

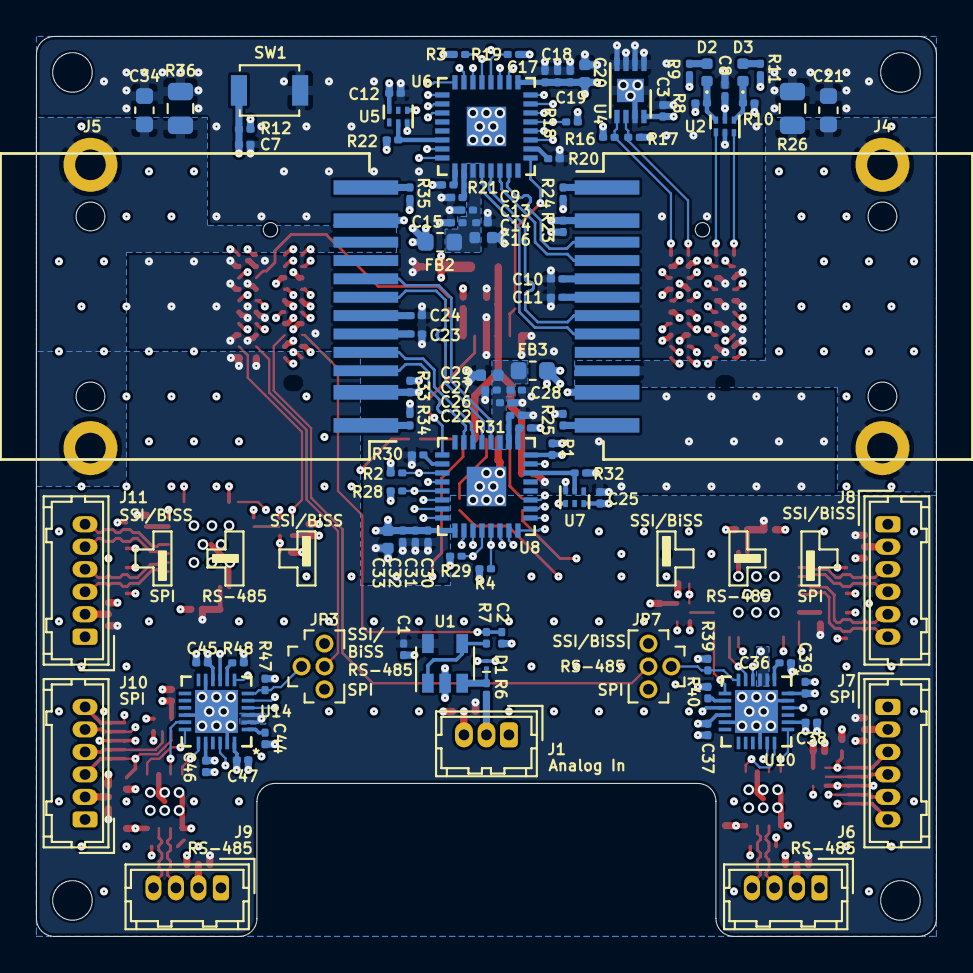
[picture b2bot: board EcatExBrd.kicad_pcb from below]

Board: 6 copper layers, 50.0 x 50.0 mm, 173 parts (104 on the bottom side), 143 nets.
